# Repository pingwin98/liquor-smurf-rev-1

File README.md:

# liquor-smurf-rev-1
 delay effect (deep blue delay based)

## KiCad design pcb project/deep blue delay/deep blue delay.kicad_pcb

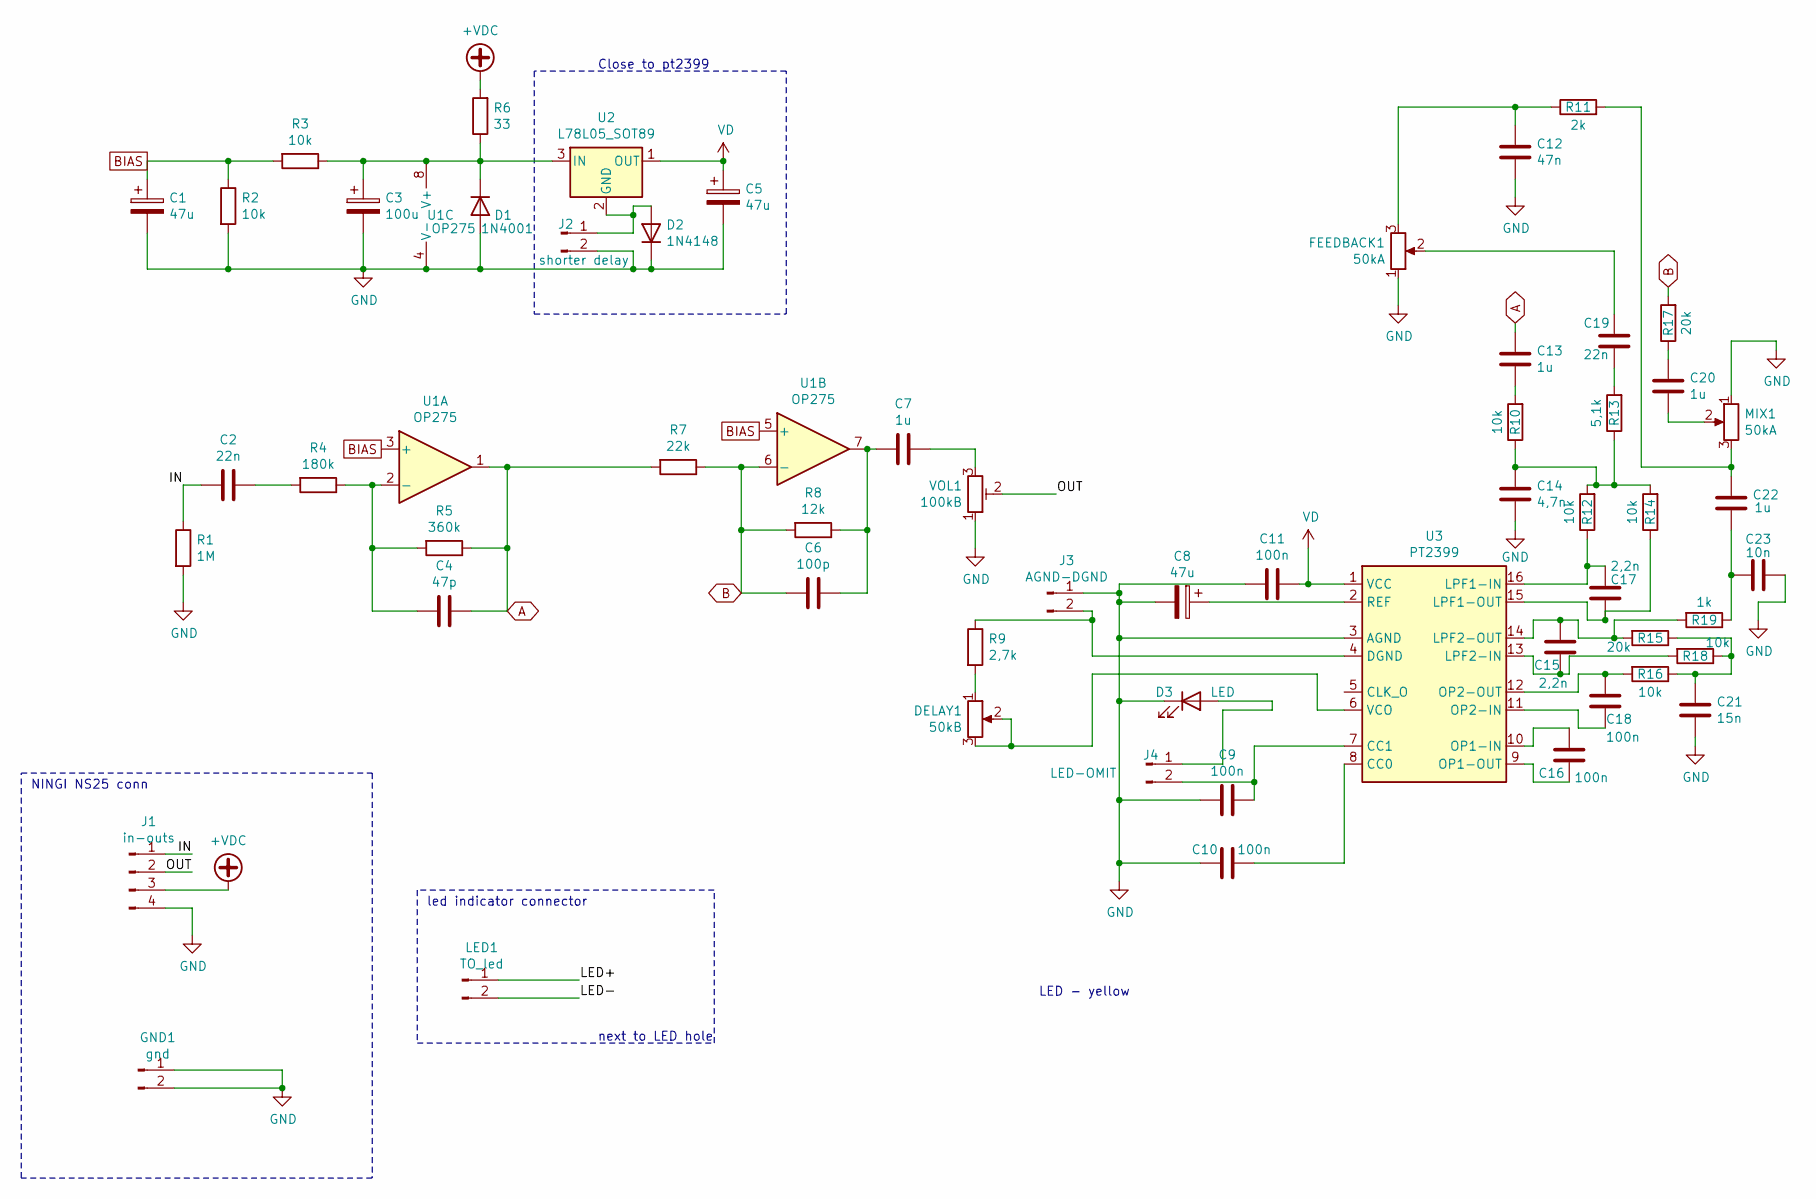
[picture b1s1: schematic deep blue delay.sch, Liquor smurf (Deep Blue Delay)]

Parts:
C1, C5, C8: 47u; CP_Radial_D5.0mm_P2.50mm
C2, C19: 22n; C_0805_2012Metric
C3: 100u; CP_Radial_D6.3mm_P2.50mm
C4: 47p; C_0805_2012Metric
C6: 100p; C_0805_2012Metric
C7, C13, C20, C22: 1u; C_Rect_L7.2mm_W5.5mm_P5.00mm_FKS2_FKP2_MKS2_MKP2
C9, C10, C11, C16, C18: 100n; C_Rect_L7.0mm_W2.5mm_P5.00mm
C12: 47n; C_0805_2012Metric
C14: 4,7n; C_0805_2012Metric
C15, C17: 2,2n; C_0805_2012Metric
C21: 15n; C_Rect_L7.0mm_W2.5mm_P5.00mm
C23: 10n; C_Rect_L7.0mm_W2.5mm_P5.00mm
D1: 1N4001; D_DO-41_SOD81_P10.16mm_Horizontal
D2: 1N4148; D_DO-35_SOD27_P7.62mm_Horizontal
D3: LED; LED_D3.0mm
DELAY1: 50kB; ALPHA-16mm_PCB-V
FEEDBACK1: 50kA; ALPHA-16mm_PCB-V
GND1: gnd; Molex_KK-254_AE-6410-02A_1x02_P2.54mm_Vertical
J1: in-outs; Molex_KK-254_AE-6410-04A_1x04_P2.54mm_Vertical
J2: shorter delay; PinHeader_1x02_P2.54mm_Vertical
J3: AGND-DGND; PinHeader_1x02_P2.54mm_Vertical
J4: LED-OMIT; PinHeader_1x02_P2.54mm_Vertical
LED1: TO_led; Molex_KK-254_AE-6410-02A_1x02_P2.54mm_Vertical
MIX1: 50kA; ALPHA-16mm_PCB-V
R1: 1M; R_1206_3216Metric
R2, R3, R10, R12, R14, R16, R18: 10k; R_1206_3216Metric
R4: 180k; R_Axial_DIN0207_L6.3mm_D2.5mm_P7.62mm_Horizontal
R5: 360k; R_Axial_DIN0207_L6.3mm_D2.5mm_P7.62mm_Horizontal
R6: 33; R_Axial_DIN0207_L6.3mm_D2.5mm_P7.62mm_Horizontal
R7: 22k; R_Axial_DIN0207_L6.3mm_D2.5mm_P7.62mm_Horizontal
R8: 12k; R_Axial_DIN0207_L6.3mm_D2.5mm_P7.62mm_Horizontal
R9: 2,7k; R_Axial_DIN0207_L6.3mm_D2.5mm_P7.62mm_Horizontal
R11: 2k; R_Axial_DIN0207_L6.3mm_D2.5mm_P7.62mm_Horizontal
R13: 5,1k; R_Axial_DIN0207_L6.3mm_D2.5mm_P7.62mm_Horizontal
R15, R17: 20k; R_Axial_DIN0207_L6.3mm_D2.5mm_P7.62mm_Horizontal
R19: 1k; R_1206_3216Metric
U1: OP275; SOIC-8_3.9x4.9mm_P1.27mm
U2: L78L05_SOT89; SOT-89-3
U3: PT2399; SOP-16_4.4x10.4mm_P1.27mm
VOL1: 100kB; Potentiometer_Piher_PT-10-V10_Vertical

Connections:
+VDC: J1.3, R6.2
/IN: C2.2, J1.1, R1.1
/LED+: LED1.1; also elsewhere on the board
/LED-: LED1.2; also elsewhere on the board
/OUT: J1.2, VOL1.2
A: C4.1, C13.1, R5.1, R7.2, U1.1
B: C6.2, R7.1, R8.2, R17.2, U1.6 (-)
BIAS: C1.1, R2.1, R3.2, U1.3 (+), U1.5 (+)
GND: C1.2, C3.2, C5.2, C8.2, C9.2, C10.2, C11.2, C12.2, C14.2, C21.2, C23.1, D1.2 (A), D2.1 (K), D3.1 (K), FEEDBACK1.1, GND1.1, GND1.2, J1.4, J2.2, J3.1, MIX1.1, R1.2, R2.2, U1.4 (V-), U3.3 (AGND), VOL1.1
unnamed: C2.1, R4.2
unnamed: C3.1, D1.1 (K), R3.1, R6.1, U1.8 (V+), U2.3 (IN)
unnamed: C4.2, R4.1, R5.2, U1.2 (-)
unnamed: C6.1, C7.2, R8.1, U1.7
unnamed: C7.1, VOL1.3
unnamed: C8.1, U3.2 (REF)
unnamed: C9.1, J4.2, U3.7 (CC1)
unnamed: C10.1, U3.8 (CC0)
unnamed: C12.1, FEEDBACK1.3, R11.1
unnamed: C13.2, R10.2
unnamed: C14.1, R10.1, R12.2, R13.1, R14.2
unnamed: C15.1, R15.2, R19.2, U3.14 (LPF2-OUT)
unnamed: C15.2, R18.2, U3.13 (LPF2-IN)
unnamed: C16.1, U3.10 (OP1-IN)
unnamed: C16.2, U3.9 (OP1-OUT)
unnamed: C17.1, R12.1, U3.16 (LPF1-IN)
unnamed: C17.2, R14.1, U3.15 (LPF1-OUT)
unnamed: C18.1, R16.2, U3.12 (OP2-OUT)
unnamed: C18.2, U3.11 (OP2-IN)
unnamed: C19.1, FEEDBACK1.2
unnamed: C19.2, R13.2
unnamed: C20.1, R17.1
unnamed: C20.2, MIX1.2
unnamed: C21.1, R15.1, R16.1, R18.1
unnamed: C22.1, MIX1.3, R11.2
unnamed: C22.2, C23.2, R19.1
unnamed: D2.2 (A), J2.1, U2.2 (GND)
unnamed: D3.2 (A), J4.1
unnamed: DELAY1.1, R9.2
unnamed: DELAY1.2, DELAY1.3, U3.6 (VCO)
unnamed: J3.2, R9.1, U3.4 (DGND)
VD: C5.1, C11.1, U2.1 (OUT), U3.1 (VCC)

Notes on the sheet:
Close to pt2399
LED - yellow
led indicator connector
next to LED hole
NINGI NS25 conn

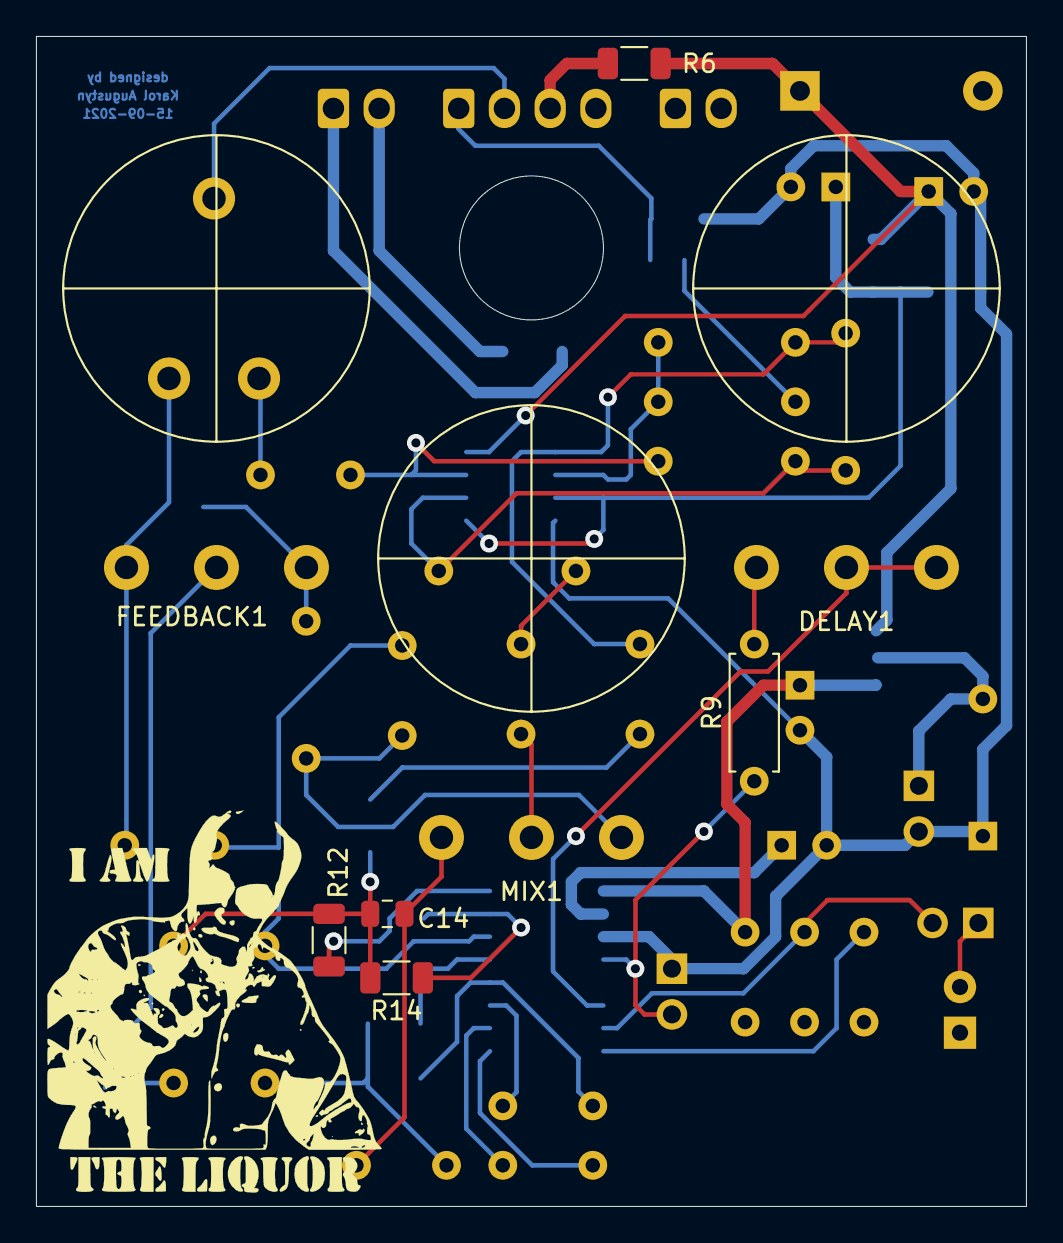
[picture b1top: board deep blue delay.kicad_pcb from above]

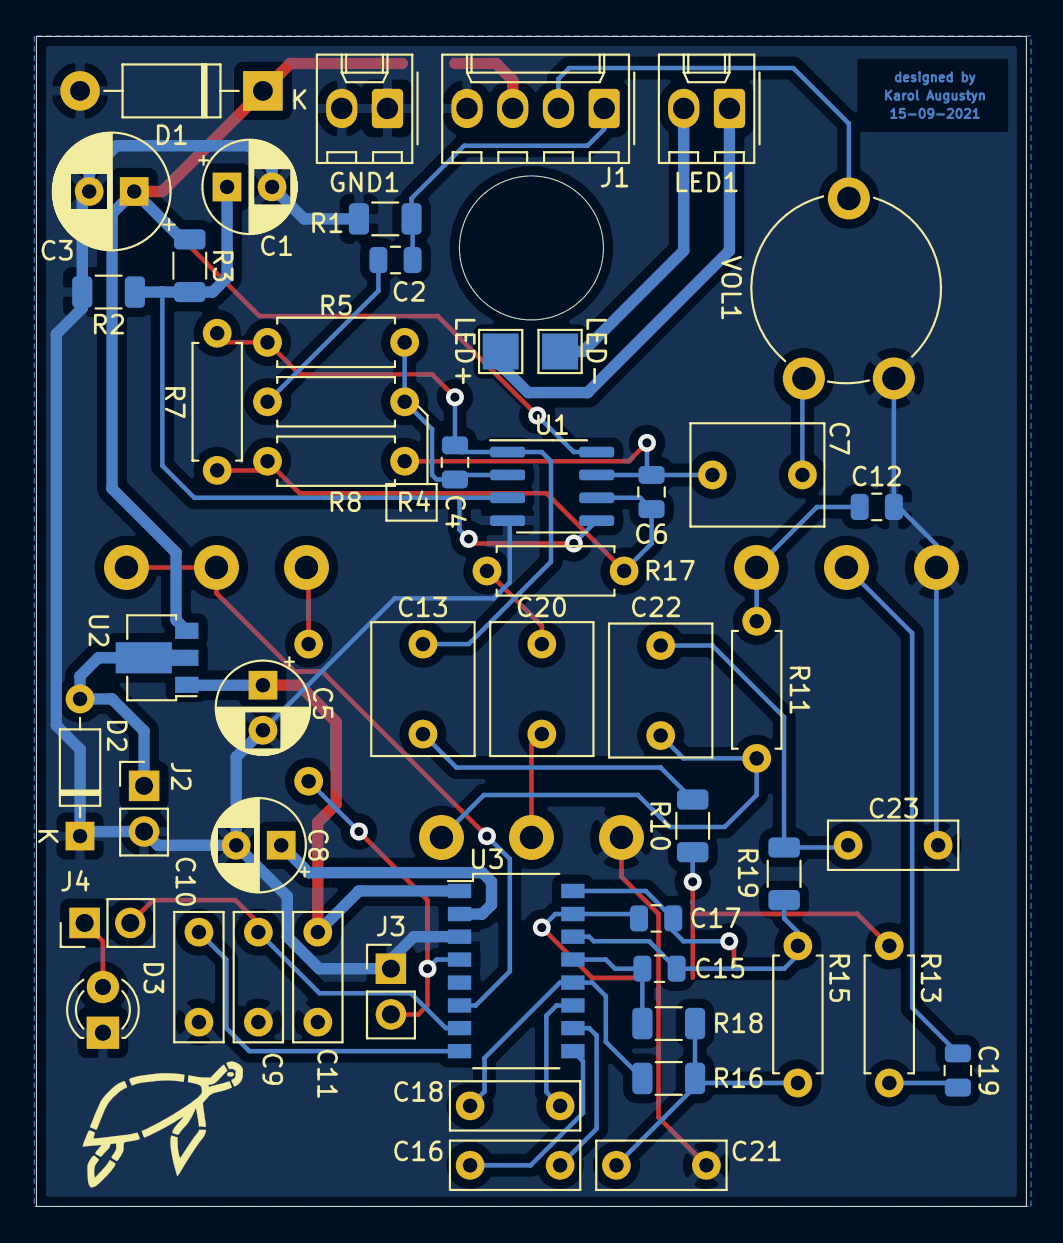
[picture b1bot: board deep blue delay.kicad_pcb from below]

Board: 2 copper layers, 55.0 x 65.0 mm, 60 parts (52 on the bottom side), 41 nets.

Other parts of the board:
LED+: TestPoint_Pad_2.0x2.0mm
LED-: TestPoint_Pad_2.0x2.0mm

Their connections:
/LED+: LED+.1; also elsewhere on the board
/LED-: LED-.1; also elsewhere on the board

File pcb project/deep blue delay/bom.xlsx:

ref | value5 | footprint | part | description | stan | link
VOL1 | 100kB | Potentiometer_THT:Potentiometer_Piher_PT-10-V10_Vertical | R_POT_TRIM | Trim-potentiometer | 2.19 | https://www.tme.eu/pl/details/pt10lv-100k/potencjometry-tht-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
C11 | 100n | Capacitor_THT:C_Rect_L7.0mm_W2.5mm_P5.00mm | C | Unpolarized capacitor | 0.25 | https://www.tme.eu/pl/details/jfh-100n/kondensatory-poliestr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
C9 | 100n | Capacitor_THT:C_Rect_L7.0mm_W2.5mm_P5.00mm | C | Unpolarized capacitor | 0.25
C10 | 100n | Capacitor_THT:C_Rect_L7.0mm_W2.5mm_P5.00mm | C | Unpolarized capacitor | 0.25
C16 | 100n | Capacitor_THT:C_Rect_L7.0mm_W2.5mm_P5.00mm | C | Unpolarized capacitor | 0.25
C18 | 100n | Capacitor_THT:C_Rect_L7.0mm_W2.5mm_P5.00mm | C | Unpolarized capacitor | 0.25
C6 | 100p | Capacitor_SMD:C_0805_2012Metric | C | Unpolarized capacitor
C3 | 100u | Capacitor_THT:CP_Radial_D6.3mm_P2.50mm | CP | Polarized capacitor
R2 | 10k | Resistor_SMD:R_1206_3216Metric | R | Resistor
R3 | 10k | Resistor_SMD:R_1206_3216Metric | R | Resistor
R16 | 10k | Resistor_SMD:R_1206_3216Metric | R | Resistor
R18 | 10k | Resistor_SMD:R_1206_3216Metric | R | Resistor
R14 | 10k | Resistor_SMD:R_1206_3216Metric | R | Resistor
R12 | 10k | Resistor_SMD:R_1206_3216Metric | R | Resistor
R10 | 10k | Resistor_SMD:R_1206_3216Metric | R | Resistor
C23 | 10n | Capacitor_THT:C_Rect_L7.0mm_W2.5mm_P5.00mm | C | Unpolarized capacitor | 0.48 | https://www.tme.eu/pl/details/b32529c1103k289/kondensatory-p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
R8 | 12k | Resistor_THT:R_Axial_DIN0207_L6.3mm_D2.5mm_P7.62mm_Horizontal | R | Resistor
C21 | 15n | Capacitor_THT:C_Rect_L7.0mm_W2.5mm_P5.00mm | C | Unpolarized capacitor | 0.5 | https://www.tme.eu/pl/details/r82ec2150dq50k/kondensatory-po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
R4 | 180k | Resistor_THT:R_Axial_DIN0207_L6.3mm_D2.5mm_P7.62mm_Horizontal | R | Resistor | 0.04 | https://www.tme.eu/pl/details/cf1_4w-180k/rezystory-weglowe-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
R19 | 1k | Resistor_SMD:R_1206_3216Metric | R | Resistor
R1 | 1M | Resistor_SMD:R_1206_3216Metric | R | Resistor
D1 | 1N4001 | Diode_THT:D_DO-41_SOD81_P10.16mm_Horizontal | 1N4001 | 50V 1A General Purpose Rectifier Diode, DO-41 | 0.2 | https://www.tme.eu/pl/details/1n4001-e3_54/diody-uniwersalne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
D2 | 1N4148 | Diode_THT:D_DO-35_SOD27_P7.62mm_Horizontal | 1N4148 | 100V 0.15A standard switching diode, DO-35 | 0.15 | https://www.tme.eu/pl/details/1n914-ons/diody-uniwersalne-th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
C7 | 1u | Capacitor_THT:C_Rect_L7.2mm_W5.5mm_P5.00mm_FKS2_FKP2_MKS2_MKP2 | C | Unpolarized capacitor
C22 | 1u | Capacitor_THT:C_Rect_L7.2mm_W5.5mm_P5.00mm_FKS2_FKP2_MKS2_MKP2 | C | Unpolarized capacitor
C20 | 1u | Capacitor_THT:C_Rect_L7.2mm_W5.5mm_P5.00mm_FKS2_FKP2_MKS2_MKP2 | C | Unpolarized capacitor
C13 | 1u | Capacitor_THT:C_Rect_L7.2mm_W5.5mm_P5.00mm_FKS2_FKP2_MKS2_MKP2 | C | Unpolarized capacitor
C15 | 2,2n | Capacitor_SMD:C_0805_2012Metric | C | Unpolarized capacitor
C17 | 2,2n | Capacitor_SMD:C_0805_2012Metric | C | Unpolarized capacitor
R9 | 2,7k | Resistor_THT:R_Axial_DIN0207_L6.3mm_D2.5mm_P7.62mm_Horizontal | R | Resistor
R15 | 20k | Resistor_THT:R_Axial_DIN0207_L6.3mm_D2.5mm_P7.62mm_Horizontal | R | Resistor | 0.4 | https://www.tme.eu/pl/details/cf1_4w-20k/rezystory-weglowe-t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
R17 | 20k | Resistor_THT:R_Axial_DIN0207_L6.3mm_D2.5mm_P7.62mm_Horizontal | R | Resistor | 0.4
R7 | 22k | Resistor_THT:R_Axial_DIN0207_L6.3mm_D2.5mm_P7.62mm_Horizontal | R | Resistor | 0.4
C2 | 22n | Capacitor_SMD:C_0805_2012Metric | C | Unpolarized capacitor
C19 | 22n | Capacitor_SMD:C_0805_2012Metric | C | Unpolarized capacitor
R11 | 2k | Resistor_THT:R_Axial_DIN0207_L6.3mm_D2.5mm_P7.62mm_Horizontal | R | Resistor | 0.4
R6 | 33 | Resistor_THT:R_Axial_DIN0207_L6.3mm_D2.5mm_P7.62mm_Horizontal | R | Resistor | 0.4
R5 | 360k | Resistor_THT:R_Axial_DIN0207_L6.3mm_D2.5mm_P7.62mm_Horizontal | R | Resistor
C14 | 4,7n | Capacitor_SMD:C_0805_2012Metric | C | Unpolarized capacitor
C12 | 47n | Capacitor_SMD:C_0805_2012Metric | C | Unpolarized capacitor
C4 | 47p | Capacitor_SMD:C_0805_2012Metric | C | Unpolarized capacitor
C1 | 47u | Capacitor_THT:CP_Radial_D5.0mm_P2.50mm | CP | Polarized capacitor
C5 | 47u | Capacitor_THT:CP_Radial_D5.0mm_P2.50mm | CP | Polarized capacitor
C8 | 47u | Capacitor_THT:CP_Radial_D5.0mm_P2.50mm | CP | Polarized capacitor
R13 | 5,1k | Resistor_THT:R_Axial_DIN0207_L6.3mm_D2.5mm_P7.62mm_Horizontal | R | Resistor | 0.4
MIX1 | 50kA | Potentiometer_THT:ALPHA-16mm_PCB-V | R_POT | Potentiometer |  | amp
FEEDBACK1 | 50kA | Potentiometer_THT:ALPHA-16mm_PCB-V | R_POT | Potentiometer |  | amp
DELAY1 | 50kB | Potentiometer_THT:ALPHA-16mm_PCB-V | R_POT | Potentiometer |  | amp
J3 | AGND-DGND | Connector_PinHeader_2.54mm:PinHeader_1x02_P2.54mm_Vertical | Conn_01x02_Male | Generic connector, single row, 01x02, script generated (kicad-library-utils/sch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 |  | na razie nie
GND1 | gnd | Connector_Molex:Molex_KK-254_AE-6410-02A_1x02_P2.54mm_Vertical | Conn_01x02_Male | Generic connector, single row, 01x02, script generated (kicad-library-utils/sch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
J1 | in-outs | Connector_Molex:Molex_KK-254_AE-6410-04A_1x04_P2.54mm_Vertical | Conn_01x04_Male | Generic connector, single row, 01x04, script generated (kicad-library-utils/sch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
U2 | L78L05_SOT89 | Package_TO_SOT_SMD:SOT-89-3 | L78L05_SOT89 | Positive 100mA 30V Linear Regulator, Fixed Output 5V, SOT-89 | 1.01
D3 | LED | LED_THT:LED_D3.0mm | LED | Light emitting diode yellow | 0.77
J4 | LED-OMIT | Connector_PinHeader_2.54mm:PinHeader_1x02_P2.54mm_Vertical | Conn_01x02_Male | Generic connector, single row, 01x02, script generated (kicad-library-utils/sch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
U1 | OP275 | Package_SO:SOIC-8_3.9x4.9mm_P1.27mm | OP275 | Dual Bipolar/JFET, Audio Operational Amplifier, DIP-8/SOIC-8 | 15
U3 | PT2399 | Package_SO:SOP-16_4.4x10.4mm_P1.27mm | PT2399 | Echo Processor IC |  | amp
J2 | shorter delay | Connector_PinHeader_2.54mm:PinHeader_1x02_P2.54mm_Vertical | Conn_01x02_Male | Generic connector, single row, 01x02, script generated (kicad-library-utils/sch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
LED1 | TO_led | Connector_Molex:Molex_KK-254_AE-6410-02A_1x02_P2.54mm_Vertical | Conn_01x02_Male | Generic connector, single row, 01x02, script generated (kicad-library-utils/sch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

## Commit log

2022-07-24 create new folder
